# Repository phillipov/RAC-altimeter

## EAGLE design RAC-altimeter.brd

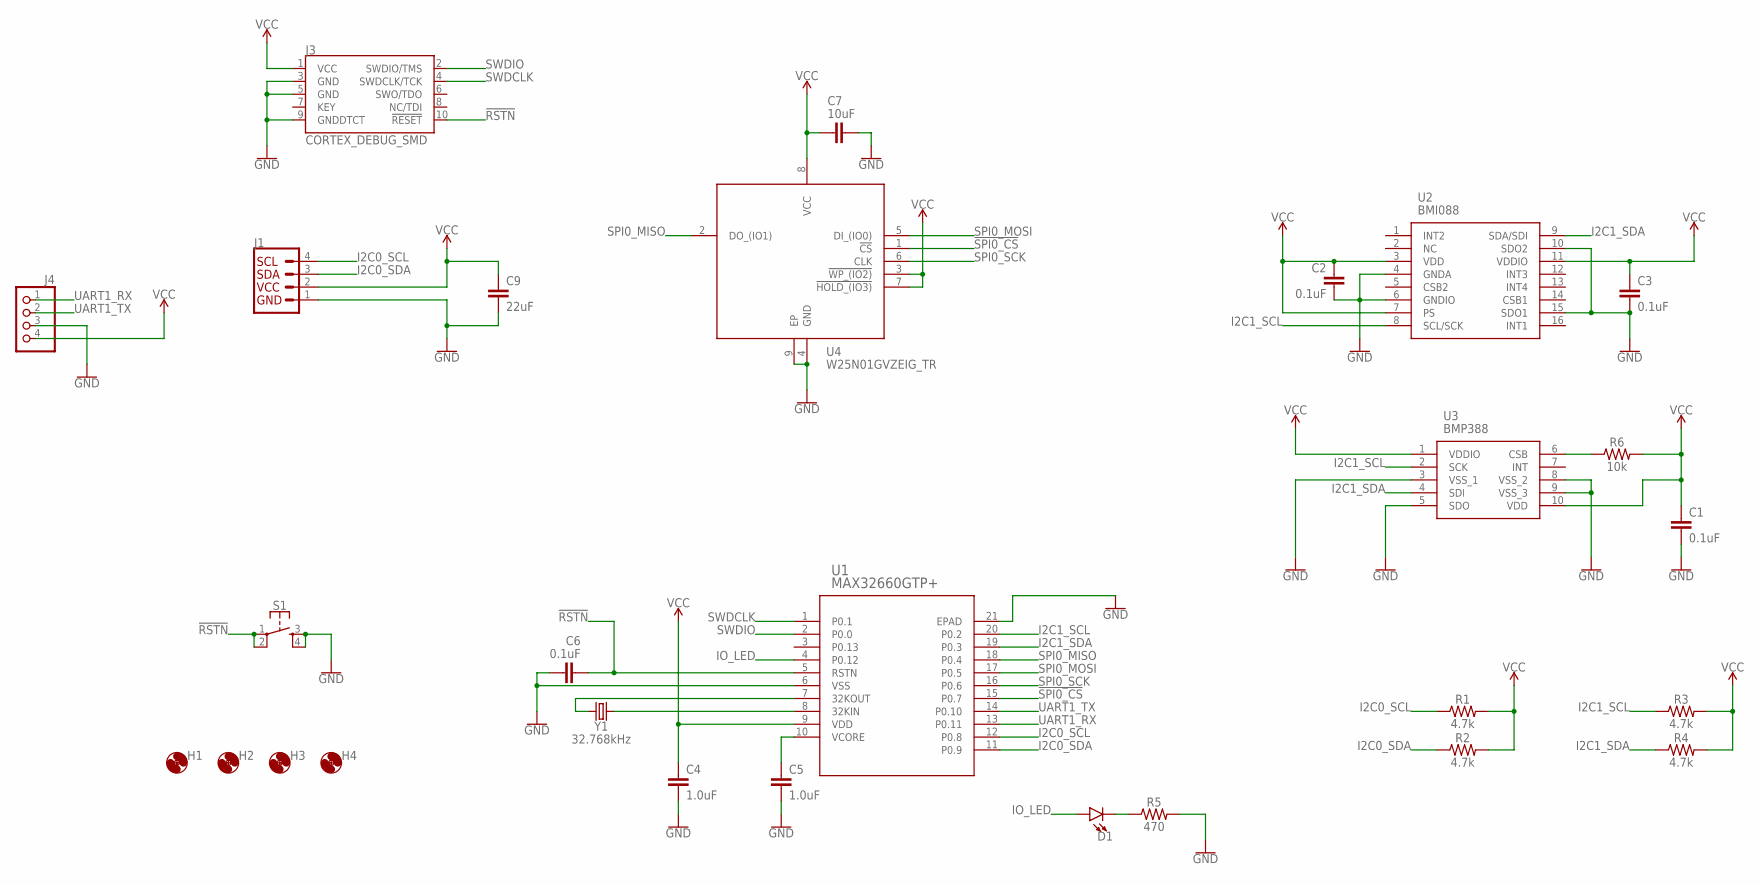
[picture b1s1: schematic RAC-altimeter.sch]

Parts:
C1, C2, C3, C6: 0.1uF; 0603
C4, C5: 1.0uF; 0603
C7: 10uF; 0603
C9: 22uF; 1210
D1: LED0603; LED-0603
H1, H2, H3, H4: MOUNT-HOLE2.8; 2,8
J1: QWIIC_CONNECTORJS-1MM; JST04_1MM_RA
J3: CORTEX_DEBUG_SMD; SAMTECH_FTSH-105-01
J4: PINHD-1X4/90; 1X04/90
R1, R2, R3, R4: 4.7k; 0603
R5: 470; 0603
R6: 10k; 0603
S1: MOMENTARY-SWITCH-SPST-2-SMD-4.6X2.8MM; TACTILE_SWITCH_SMD_4.6X2.8MM
U1: MAX32660GTP+; 21-0139V_T2044+5
U2: BMI088
U3: BMP388
U4: W25N01GVZEIG_TR; SON127P800X600X80-9N
Y1: 32.768kHz; CRYSTAL-SMD-3.2X1.5MM

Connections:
32KIN: U1.8 (32KIN), Y1.P$1 (1)
32KOUT: U1.7 (32KOUT), Y1.P$2 (2)
!RSTN: C6.1, J3.10 (!RESET), S1.1, S1.2, U1.5 (RSTN)
!SPI0_CS: U1.15 (P0.7), U4.1 (!CS)
BMP_CS: R6.1, U3.6 (CSB)
GND: C1.2, C2.2, C3.1, C4.2, C5.2, C6.2, C7.2, C9.2, J1.1, J3.3 (GND), J3.5 (GND), J3.9 (GNDDTCT), J4.3, R5.2, S1.3, S1.4, U1.6 (VSS), U1.21 (EPAD), U2.4 (GNDA), U2.6 (GNDIO), U2.10 (SDO2), U2.15 (SDO1), U3.3 (VSS_1), U3.5 (SDO), U3.8 (VSS_2), U3.9 (VSS_3), U4.4 (GND), U4.9 (EP)
I2C0_SCL: J1.4, R1.1, U1.12 (P0.8)
I2C0_SDA: J1.3, R2.1, U1.11 (P0.9)
I2C1_SCL: R3.1, U1.20 (P0.2), U2.8 (SCL/SCK), U3.2 (SCK)
I2C1_SDA: R4.1, U1.19 (P0.3), U2.9 (SDA/SDI), U3.4 (SDI)
IO_LED: D1.A, U1.4 (P0.12)
LED_CATH: D1.C, R5.1
SPI0_MISO: U1.18 (P0.4), U4.2 (DO_(IO1))
SPI0_MOSI: U1.17 (P0.5), U4.5 (DI_(IO0))
SPI0_SCK: U1.16 (P0.6), U4.6 (CLK)
SWDCLK: J3.4 (SWDCLK/TCK), U1.1 (P0.1)
SWDIO: J3.2 (SWDIO/TMS), U1.2 (P0.0)
UART1_RX: J4.1, U1.13 (P0.11)
UART1_TX: J4.2, U1.14 (P0.10)
VCC: C1.1, C2.1, C3.2, C4.1, C7.1, C9.1, J1.2, J3.1 (VCC), J4.4, R1.2, R2.2, R3.2, R4.2, R6.2, U1.9 (VDD), U2.3 (VDD), U2.7 (PS), U2.11 (VDDIO), U3.1 (VDDIO), U3.10 (VDD), U4.3 (!WP_(IO2)), U4.7 (!HOLD_(IO3)), U4.8 (VCC)
VCORE: C5.1, U1.10 (VCORE)

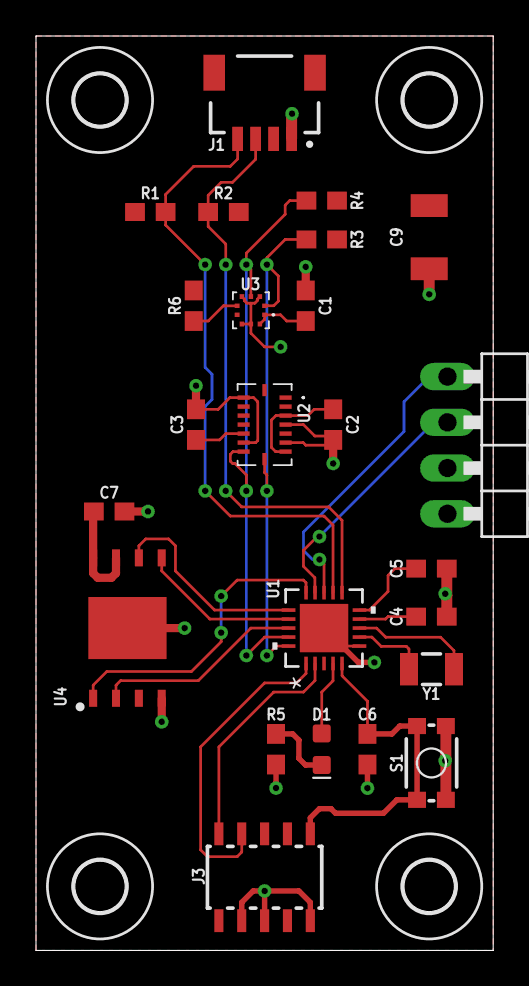
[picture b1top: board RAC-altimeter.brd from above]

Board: 2 copper layers, 25.4 x 50.8 mm, 28 parts (0 on the bottom side), 21 nets.

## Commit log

2019-04-21 Added altimeter and MCU
2019-04-22 Added decoupling capacitors to BMP388
2019-05-05 Added SD Card, rewired BMP388 for I2C
2019-05-21 Replaced MAX32660 with STM32L412 MCU
2019-06-07 Connected the BMI088 IMU, removed pull-up on SD data line
2019-06-08 Connected the TPS73733 LDO
2019-07-28 Re-integrated the MAX32660 in a 20-pin package
2019-07-28 Integrated the RN4871 bluetooth module
2019-07-29 Replaced the LDO with a TPS62172 buck converter
2019-07-29 Replaced the buck converter with the MCP1640 boost converter
2019-07-31 Added SWD 10-pin header, battery terminals, and GPIO LED
2019-08-03 Added reset button, power enable switch, and power enable jumper
2019-08-03 Cleaned up the schematic arrangement
2019-08-03 Started a board file
2019-08-04 Fixed net connections and routed IC groups
2019-08-04 Added PCB mounting holes
2019-08-04 Closed loose nets and finished routing
2019-08-05 Replaced the SD card socket with a NAND flash IC
2019-08-17 Fully routed board with the SPI flash IC
2019-08-18 Laid out parts neatly, routed board, removed unnecessary parts
2019-08-23 Removed RF and boost subsystems, added a spare I2C bus and two JST connectors
2019-08-23 Added UART console pinheaders
2019-08-23 Reordered component numbers
2019-08-23 Fixed two more component numbers and added 22uF bulk decoupling
2019-08-24 Cleaned out dir before merging
2019-08-24 Removed board file
2019-08-24 Created board file after merging
2019-08-24 Organized board for layout
2019-08-24 Swapped I2C0 and I2C1 bus connections for better routing
2019-08-24 Partially routed board
2019-08-24 Completely routed board
2019-08-25 Removed spare JST connector and BMP388 capacitor; redid IC placement
2019-08-25 Finished routing board, cleared DRC

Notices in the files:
parts and their libraries:
SparkFun-Capacitors: Licensing: Creative Commons ShareAlike 4.0 International - https://creativecommons.org/licenses/by-sa/4.0
